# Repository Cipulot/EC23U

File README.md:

# EC23U

Open source numpad Electrostatic Capacitive PCB.

## Introduction

This project is a continuation of my development of open source EC boards.

The supported layout options are the following:

## Technical information

- Layout size: 23U layouts with alternative options
- Compatible switches: EC switches (Topre and NIZ)
- Microcontroller: STM32F401
- Connector: Original OEM JST connector
- Firmware compatibility: QMK (with VIA/VIAL support)
- Protection hardware (present on both the mainboard and both controller versions):
  - Fused
  - ESD protection
- Addressable RGB LED support
- Numlock LED support

## Renders and Prototypes

### Render

### Prototypes

**NOTE**: The silkscreen text near the JST connector has the `GND` and `VBUS` label swapped. This is wrong and have been fixed in the latest revision.

## Revisions and relative features

### Rev1.0

This revision implements all the main features of the mainboard ad controllers mentioned in the specifications.

#### RGB header

The mainboard features an RGB header for connecting +5V addressable RGB strips. THe properties of the lighting can be controlled through Vial or by assigning RGB control keycodes on the board itself.

#### NumLock Indicator

The mainboard features a NumLock indicator LED. The LED is controlled by the MCU and reacts based on the system state. The LED used is a 3.0mm THT LED. Polarity is signalled by the silkscreen. The indicator is optional.

#### DFU

To access the DFU mode of the mainboard you can perform one of the following actions:

- press the key to which the `QK_BOOT` keycode is assigned (if available)
- while plugging in the board short the `Boot0` pins on the mainboard

## PCB order procedure

### Production files

The production can be found in the [Production folder](/Production).

In there you'll find the main PCB files and the JIS and HHKB plates.

As usual the `*.zip` files are the gerber files, `BOM-*.csv` are the BOM (Bill Of Material) files and `POS-*.csv` are the POS/CPL (Footprint POSition/Component Placement List) files.

### Assembly options

Here follows the options to be used for assembly:

- Assembly Side: Bottom
- Confirm Parts Placement: `yes`

## Copyright notice

This project is not endorse nor sponsored in any way by Topre Corporation and PFU Limited. The HHKB Logo and Topre logo are trademarks of their respective owners.

## License

<br />This work is licensed under a <a rel="license" href="http://creativecommons.org/licenses/by-nc-sa/4.0/">Creative Commons Attribution-NonCommercial-ShareAlike 4.0 International License</a>.

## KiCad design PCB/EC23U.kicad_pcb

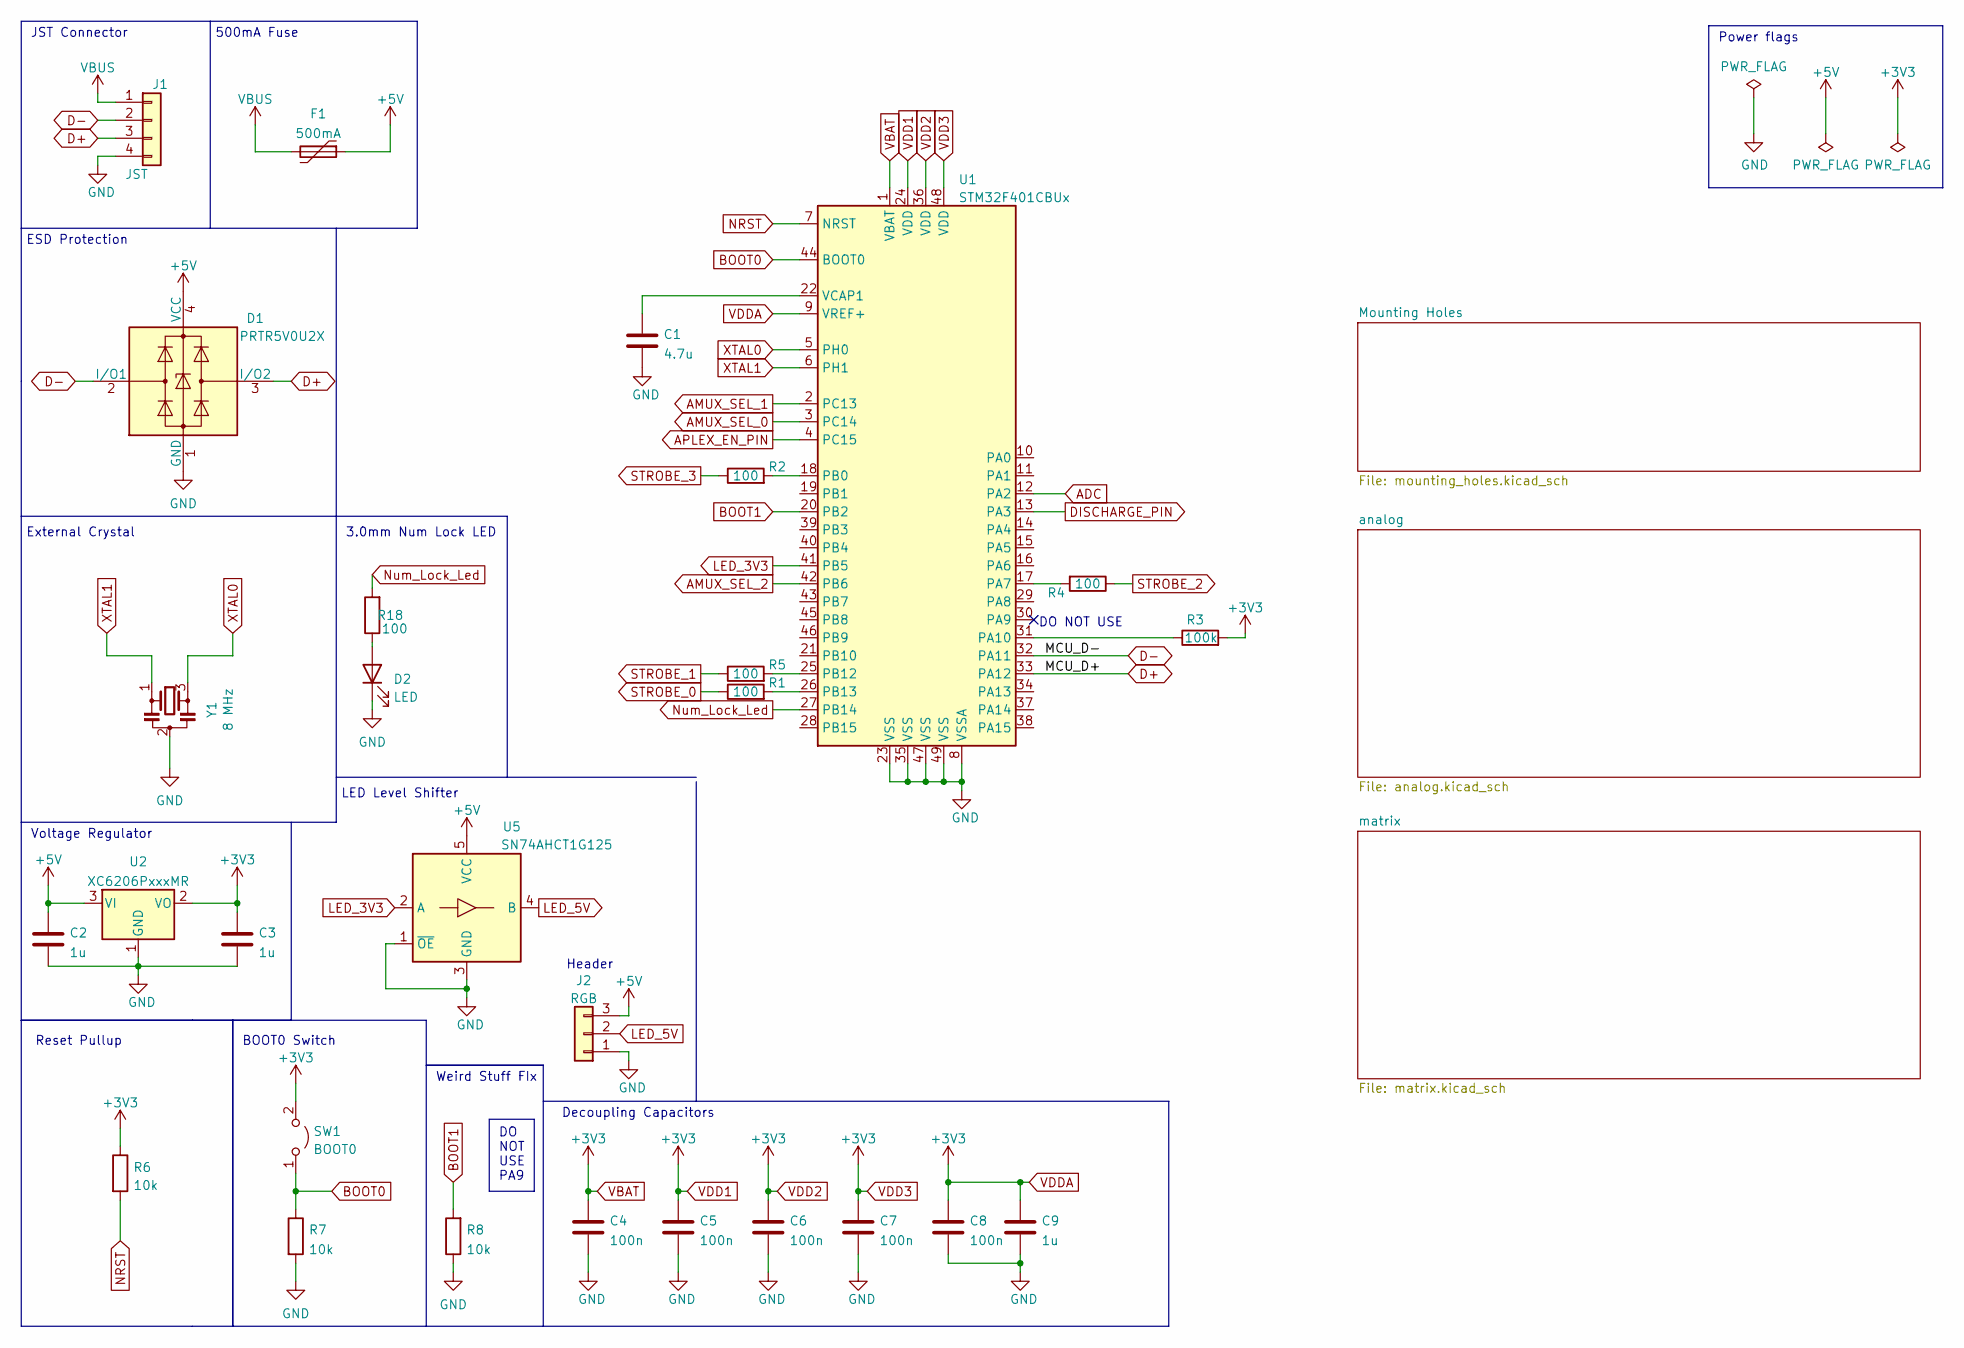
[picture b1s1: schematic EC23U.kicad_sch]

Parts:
C1: 4.7u; C_0402_1005Metric; LCSC C23733
C2, C3, C9: 1u; C_0402_1005Metric; LCSC C52923
C4, C5, C6, C7, C8: 100n; C_0402_1005Metric; LCSC C307331
D1: PRTR5V0U2X; SOT-143; LCSC C2827688
D2: LED; LED_D3.0mm
F1: 500mA; Fuse_0603_1608Metric; LCSC C720073
J1: JST; JST_EH_S4B-EH_1x04_P2.50mm_Horizontal; LCSC C265068
J2: RGB; PinSocket_1x03_P2.54mm_Vertical
R1, R2, R4, R5, R18: 100; R_0402_1005Metric; LCSC C25076
R3: 100k; R_0402_1005Metric; LCSC C25741
R6, R7, R8: 10k; R_0402_1005Metric; LCSC C25744
SW1: BOOT0; PinHeader_1x02_P2.00mm_Vertical
U1: STM32F401CBUx; QFN-48-1EP_7x7mm_P0.5mm_EP5.6x5.6mm; LCSC C118825
U2: XC6206PxxxMR; SOT-23; LCSC C5446
U5: SN74AHCT1G125; SOT-23-5; LCSC C7484
Y1: 8 MHz; Resonator_SMD_Murata_CSTxExxV-3Pin_3.0x1.1mm; LCSC C907975

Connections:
+5V: C2.1, D1.4 (VCC), F1.1, J2.3, U2.3 (VI), U5.5 (VCC)
ADC: U1.12 (PA2); also elsewhere on the board
AMUX_SEL_0: U1.3 (PC14); also elsewhere on the board
AMUX_SEL_1: U1.2 (PC13); also elsewhere on the board
AMUX_SEL_2: U1.42 (PB6); also elsewhere on the board
APLEX_EN_PIN: U1.4 (PC15); also elsewhere on the board
APLEX_OUT_PIN: U1.13 (PA3); also elsewhere on the board
BOOT0: R7.1, SW1.1 (A), U1.44 (BOOT0)
BOOT1: R8.2, U1.20 (PB2)
D+: D1.3 (I/O2), J1.3, U1.33 (PA12)
D-: D1.2 (I/O1), J1.2, U1.32 (PA11)
GND: C1.2, C2.2, C3.2, C4.2, C5.2, C6.2, C7.2, C8.2, C9.2, D1.1 (GND), D2.1 (K), J1.4, J2.1, R7.2, R8.1, U1.8 (VSSA), U1.23 (VSS), U1.35 (VSS), U1.47 (VSS), U1.49 (VSS), U2.1 (GND), U5.1 (~OE), U5.3 (GND), Y1.2; also elsewhere on the board
LED_3V3: U1.41 (PB5), U5.2 (A)
LED_5V: J2.2, U5.4 (B)
NRST: R6.2, U1.7 (NRST)
unnamed: D2.2 (A), R18.1
unnamed: R4.2, U1.17 (PA7)
unnamed: R3.1, U1.31 (PA10)
unnamed: R2.2, U1.18 (PB0)
unnamed: R5.2, U1.25 (PB12)
unnamed: R1.2, U1.26 (PB13)
unnamed: C1.1, U1.22 (VCAP1)
Num_Lock_Led: R18.2, U1.27 (PB14)
STROBE_0: R1.1; also elsewhere on the board
STROBE_1: R5.1; also elsewhere on the board
STROBE_2: R4.1; also elsewhere on the board
STROBE_3: R2.1; also elsewhere on the board
VBAT: C3.1, C4.1, C5.1, C6.1, C7.1, C8.1, C9.1, R3.2, R6.1, SW1.2 (B), U1.1 (VBAT), U1.9 (VREF+), U1.24 (VDD), U1.36 (VDD), U1.48 (VDD), U2.2 (VO); also elsewhere on the board
VBUS: F1.2, J1.1
XTAL0: U1.5 (PH0), Y1.3
XTAL1: U1.6 (PH1), Y1.1

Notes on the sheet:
Voltage Regulator
Weird Stuff FIx
3.0mm Num Lock LED
Decoupling Capacitors
BOOT0 Switch
DO NOT USE
DO NOT USE PA9
LED Level Shifter
External Crystal
500mA Fuse
Header
JST Connector
ESD Protection
Reset Pullup
Power flags

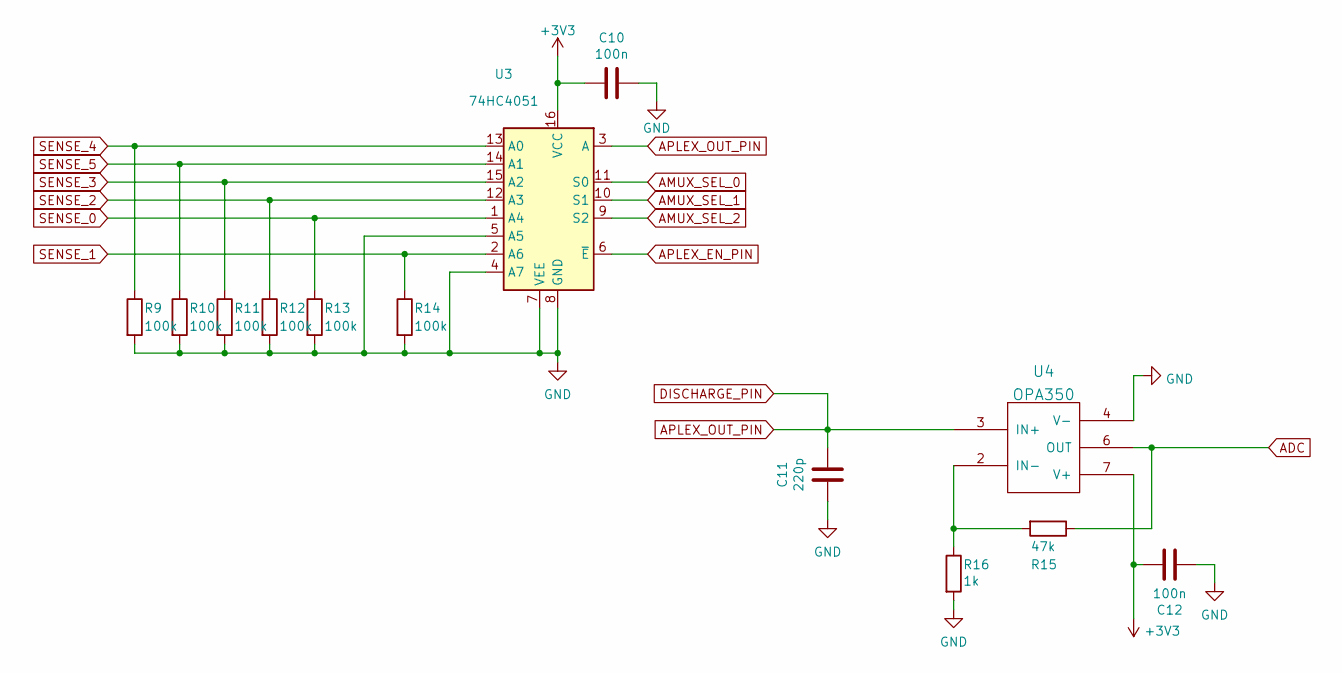
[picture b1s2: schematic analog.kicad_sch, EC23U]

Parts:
C10, C12: 100n; C_0402_1005Metric; LCSC C307331
C11: 220p; C_0402_1005Metric; LCSC C1530
R9, R10, R11, R12, R13, R14: 100k; R_0402_1005Metric; LCSC C25741
R15: 47k; R_0402_1005Metric; LCSC C25792
R16: 1k; R_0402_1005Metric; LCSC C11702
U3: 74HC4051; TSSOP16; LCSC C5645
U4: OPA350; SOIC-8_3.9x4.9mm_P1.27mm; LCSC C13388

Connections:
ADC: R15.1, U4.6 (OUT); also elsewhere on the board
AMUX_SEL_0: U3.11 (S0); also elsewhere on the board
AMUX_SEL_1: U3.10 (S1); also elsewhere on the board
AMUX_SEL_2: U3.9 (S2); also elsewhere on the board
APLEX_EN_PIN: U3.6 (~E); also elsewhere on the board
APLEX_OUT_PIN: C11.1, U3.3 (A), U4.3 (IN+); also elsewhere on the board
GND: C10.1, C11.2, C12.1, R9.2, R10.2, R11.2, R12.2, R13.2, R14.2, R16.2, U3.4 (A7), U3.5 (A5), U3.7 (VEE), U3.8 (GND), U4.4 (V-); also elsewhere on the board
unnamed: R15.2, R16.1, U4.2 (IN-)
SENSE_0: R13.1, U3.1 (A4); also elsewhere on the board
SENSE_1: R14.1, U3.2 (A6); also elsewhere on the board
SENSE_2: R12.1, U3.12 (A3); also elsewhere on the board
SENSE_3: R11.1, U3.15 (A2); also elsewhere on the board
SENSE_4: R9.1, U3.13 (A0); also elsewhere on the board
SENSE_5: R10.1, U3.14 (A1); also elsewhere on the board
VBAT: C10.2, C12.2, U3.16 (VCC), U4.7 (V+); also elsewhere on the board

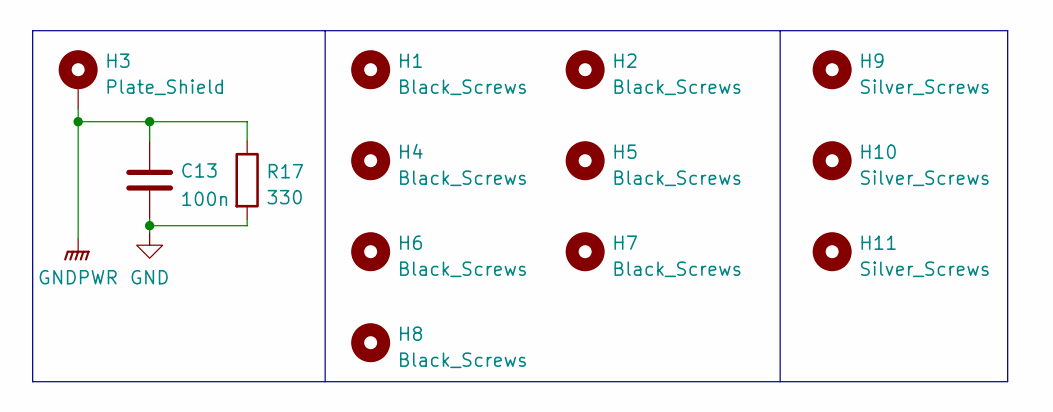
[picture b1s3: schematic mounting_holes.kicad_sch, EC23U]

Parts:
C13: 100n; C_0402_1005Metric; LCSC C307331
H1, H2, H4, H5, H6, H7, H8: Black_Screws; HOLE_M2_RF
H3: Plate_Shield; MountingHole_2.2mm_M2_Pad
H9, H10, H11: Silver_Screws; HOLE_M2_RF
R17: 330; C_0402_1005Metric; LCSC C25104

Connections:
GND: C13.2, R17.2; also elsewhere on the board
GNDPWR: C13.1, H3.1, R17.1

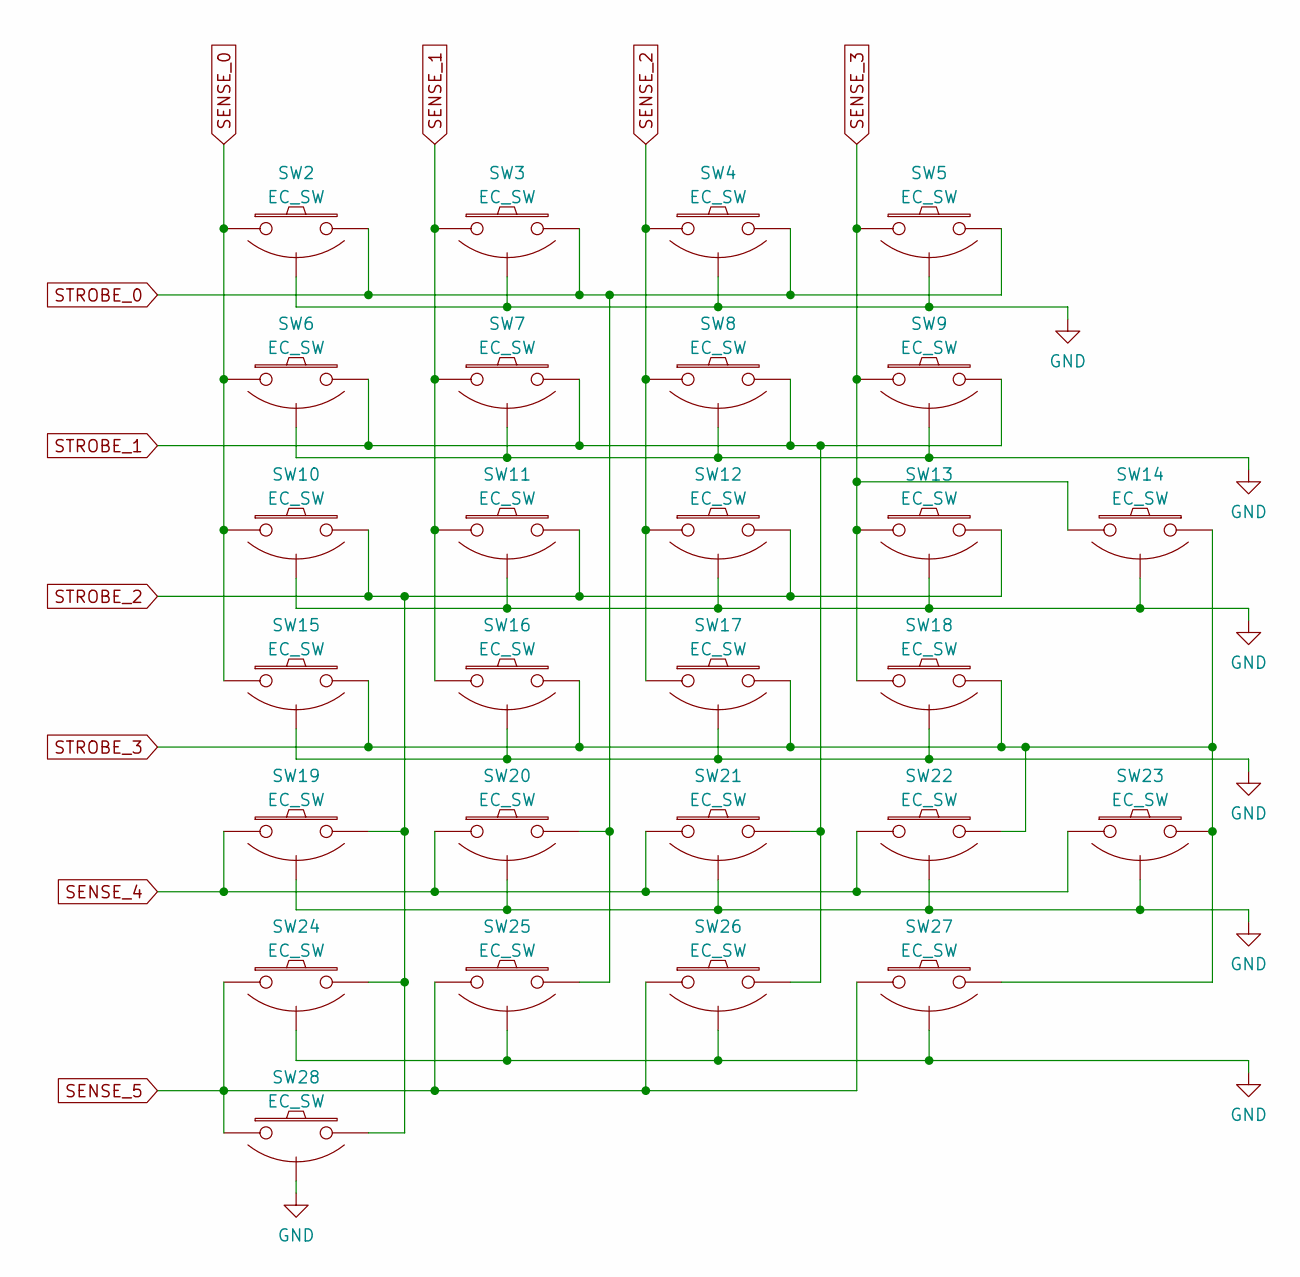
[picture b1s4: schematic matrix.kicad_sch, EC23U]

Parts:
SW2, SW3, SW4, SW5, SW6, SW7, SW8, SW9, SW10, SW11, SW12, SW13, SW15, SW16, SW17, SW18, SW19, SW20, SW21, SW22, SW24, SW25, SW26, SW27: EC_SW; ecs_pad_1U_no_ring
SW14, SW23, SW28: EC_SW; ecs_pad_2U_no_ring

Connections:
GND: SW2.3 (SG), SW3.3 (SG), SW4.3 (SG), SW5.3 (SG), SW6.3 (SG), SW7.3 (SG), SW8.3 (SG), SW9.3 (SG), SW10.3 (SG), SW11.3 (SG), SW12.3 (SG), SW13.3 (SG), SW14.3 (SG), SW15.3 (SG), SW16.3 (SG), SW17.3 (SG), SW18.3 (SG), SW19.3 (SG), SW20.3 (SG), SW21.3 (SG), SW22.3 (SG), SW23.3 (SG), SW24.3 (SG), SW25.3 (SG), SW26.3 (SG), SW27.3 (SG), SW28.3 (SG); also elsewhere on the board
SENSE_0: SW2.1, SW6.1, SW10.1, SW15.1; also elsewhere on the board
SENSE_1: SW3.1, SW7.1, SW11.1, SW16.1; also elsewhere on the board
SENSE_2: SW4.1, SW8.1, SW12.1, SW17.1; also elsewhere on the board
SENSE_3: SW5.1, SW9.1, SW13.1, SW14.2, SW18.1; also elsewhere on the board
SENSE_4: SW19.1, SW20.1, SW21.1, SW22.1, SW23.1; also elsewhere on the board
SENSE_5: SW24.1, SW25.1, SW26.1, SW27.1, SW28.1; also elsewhere on the board
STROBE_0: SW2.2, SW3.2, SW4.2, SW5.2, SW20.2, SW25.2; also elsewhere on the board
STROBE_1: SW6.2, SW7.2, SW8.2, SW9.2, SW21.2, SW26.2; also elsewhere on the board
STROBE_2: SW10.2, SW11.2, SW12.2, SW13.2, SW19.2, SW24.2, SW28.2; also elsewhere on the board
STROBE_3: SW14.1, SW15.2, SW16.2, SW17.2, SW18.2, SW22.2, SW23.2, SW27.2; also elsewhere on the board

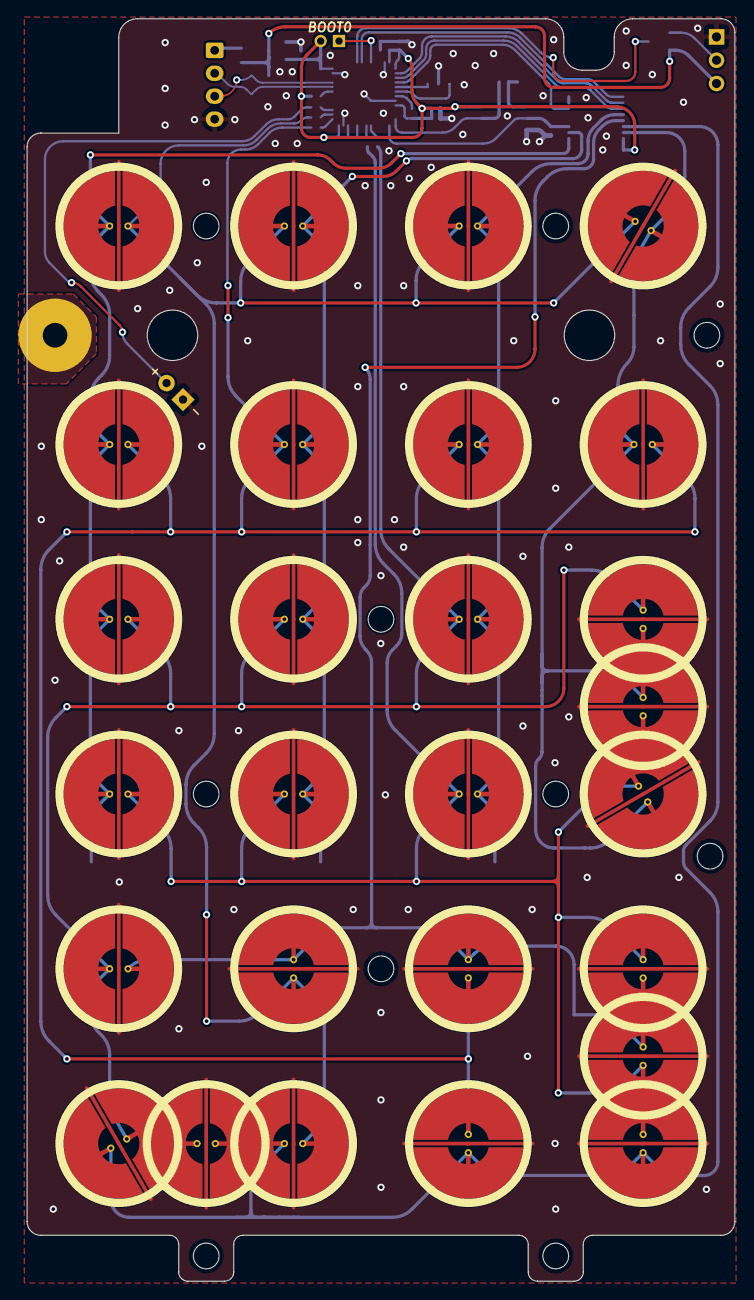
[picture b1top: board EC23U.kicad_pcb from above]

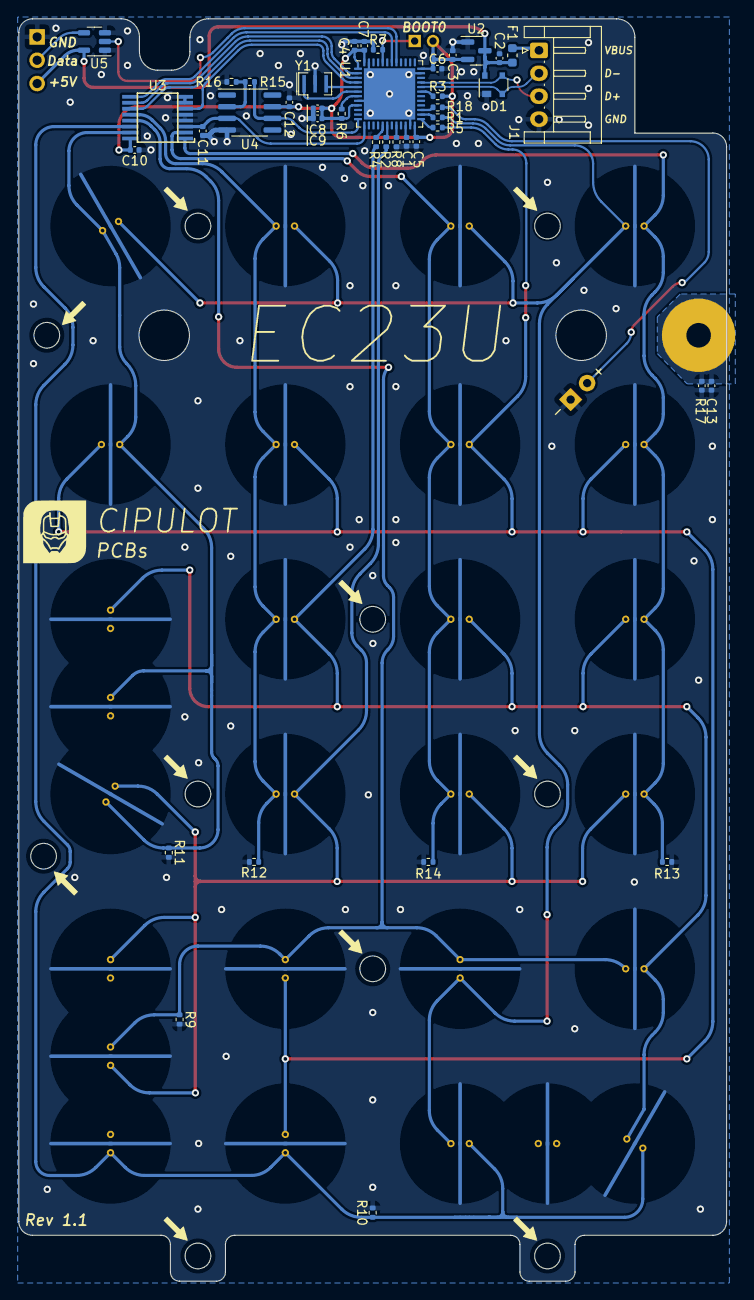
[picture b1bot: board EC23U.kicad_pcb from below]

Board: 2 copper layers, 77.1 x 137.6 mm, 81 parts (40 on the bottom side), 39 nets.

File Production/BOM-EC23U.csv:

Comment,Designator,Footprint,LCSC
1k,R16,R_0402_1005Metric,C11702
STM32F401CBUx,U1,QFN-48-1EP_7x7mm_P0.5mm_EP5.6x5.6mm,C118825
OPA350,U4,SOIC-8_3.9x4.9mm_P1.27mm,C13388
220p,C11,C_0402_1005Metric,C1530
4.7u,C1,C_0402_1005Metric,C23733
100,"R1,R18,R2,R4,R5",R_0402_1005Metric,C25076
330,R17,C_0402_1005Metric,C25104
100k,"R10,R11,R12,R13,R14,R3,R9",R_0402_1005Metric,C25741
10k,"R6,R7,R8",R_0402_1005Metric,C25744
47k,R15,R_0402_1005Metric,C25792
JST,J1,JST_EH_S4B-EH_1x04_P2.50mm_Horizontal,C265068
PRTR5V0U2X,D1,SOT-143,C2827688
100n,"C10,C12,C13,C4,C5,C6,C7,C8",C_0402_1005Metric,C307331
1u,"C2,C3,C9",C_0402_1005Metric,C52923
XC6206PxxxMR,U2,SOT-23,C5446
74HC4051,U3,TSSOP16,C5645
500mA,F1,Fuse_0603_1608Metric,C720073
SN74AHCT1G125,U5,SOT-23-5,C7484
8 MHz,Y1,Resonator_SMD_Murata_CSTxExxV-3Pin_3.0x1.1mm,C907975

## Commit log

2023-02-23 Kicad 7 update and change of resistor value
2023-03-20 VIA Update
    VIA firmware update.
2023-03-24 Delete ec_23u.json
    Added to VIA main.
2023-07-15 Updated to `Rev 1.1`
    Updated the title block in schematics to reflect company name and updated EC pads to latest model.
    This update isn't critical, hence the lack of proper `Rev` update in README.
2023-08-19 Addition of new FW
    New Sideload firmware release that enables new features as:
    - Rapid Trigger (still WIP with bugs)
    - Calibration
    Compatible with previous revisions PCBs.
2023-11-03 Firmware folder update
2023-11-15 Update LICENSE
2023-11-17 Updated sheets
2023-12-21 Update FW
2024-03-03 Update
    Updated the License for the project and relative details.
2024-03-03 Update LICENSE
    Fix formatting
2024-06-05 EC23U Cleanup

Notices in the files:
PCB/EC23U.kicad_pcb:
CC-BY-NC-SA-4.0
